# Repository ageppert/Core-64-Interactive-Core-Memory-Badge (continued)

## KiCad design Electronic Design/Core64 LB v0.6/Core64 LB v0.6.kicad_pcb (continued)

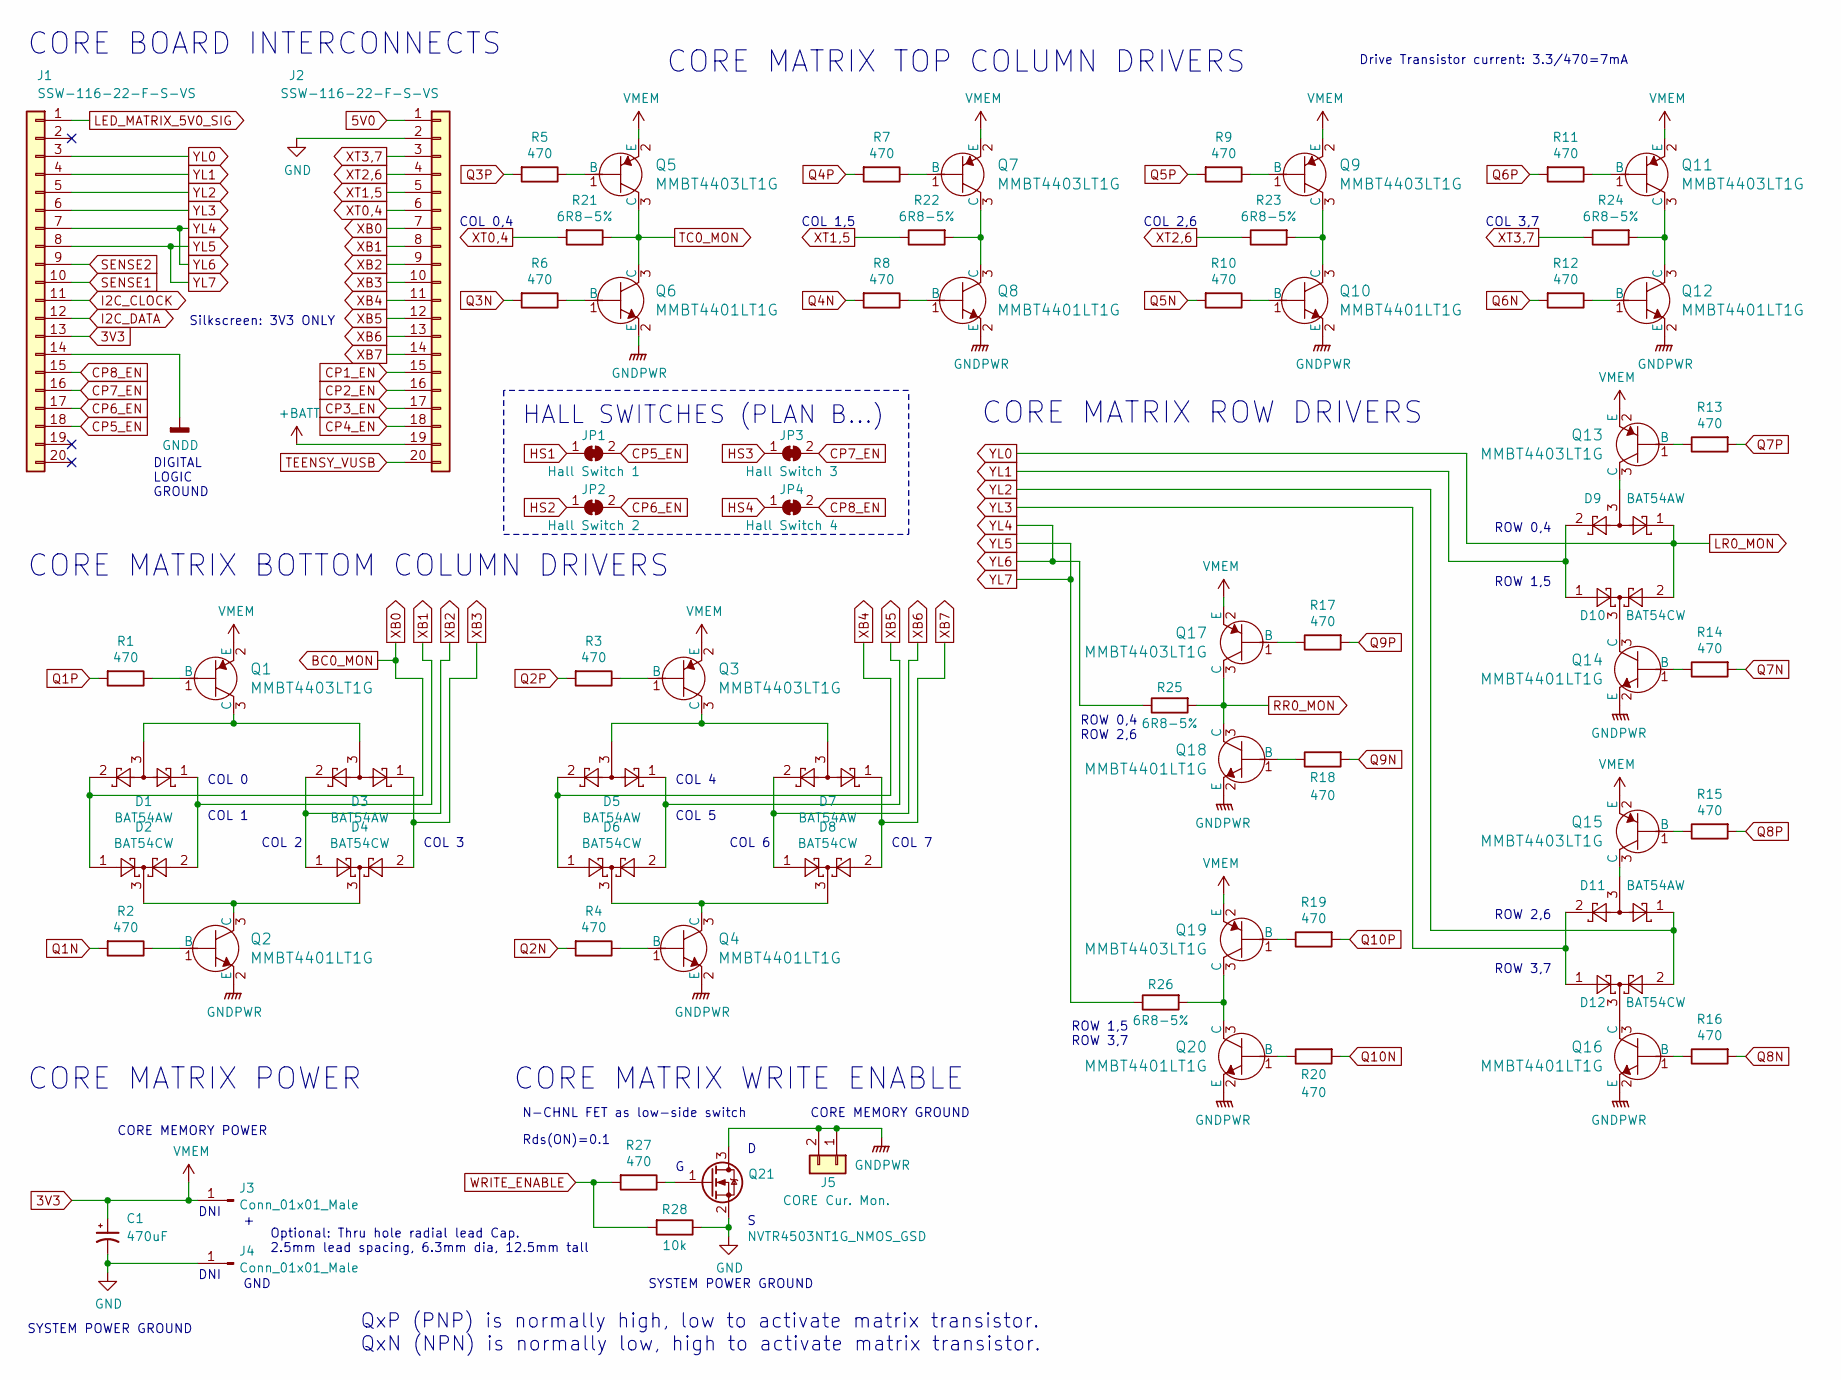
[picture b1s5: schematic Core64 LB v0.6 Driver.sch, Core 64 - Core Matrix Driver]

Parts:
C1: 470uF; CP_Elec_6.3x7.7; MPN(Secondary) 6.3SEV330M6.3X8; Digikey 565-EMHL100ARA471MHA0GCT-ND
D1, D3, D5, D7, D9, D11: BAT54AW; SOT-323_SC-70; MPN BAT54AW-7-F
D2, D4, D6, D8, D10, D12: BAT54CW; SOT-323_SC-70; MPN BAT54CW-7-F
J1, J2: SSW-116-22-F-S-VS‎; PinSocket_1x20_P2.54mm_Vertical
J3, J4: Conn_01x01_Male; PinHeader_1x01_P2.54mm_Vertical_No_Registration
J5: CORE Cur. Mon.; PinSocket_1x02_P2.54mm_Vertical
JP1: Hall Switch 1; SolderJumper-2_P1.3mm_Bridged_RoundedPad1.0x1.5mm
JP2: Hall Switch 2; SolderJumper-2_P1.3mm_Bridged_RoundedPad1.0x1.5mm
JP3: Hall Switch 3; SolderJumper-2_P1.3mm_Bridged_RoundedPad1.0x1.5mm
JP4: Hall Switch 4; SolderJumper-2_P1.3mm_Bridged_RoundedPad1.0x1.5mm
Q1, Q3, Q5, Q7, Q9, Q11, Q13, Q15, Q17, Q19: MMBT4403LT1G; SOT-23-3; MPN MMBT4403LT1G; Digi-Key_PN MMBT4403LT1GOSCT-ND
Q2, Q4, Q6, Q8, Q10, Q12, Q14, Q16, Q18, Q20: MMBT4401LT1G; SOT-23-3; MPN MMBT4401LT1G; Digi-Key_PN MMBT4401LT1GOSCT-ND
Q21: NVTR4503NT1G_NMOS_GSD; SOT-23-3; MPN NVTR4503NT1G
R1, R2, R3, R4, R5, R6, R7, R8, R9, R10, R11, R12, R13, R14, R15, R16, R17, R18, R19, R20, R27: 470; R_0805_2012Metric
R21, R22, R23, R24, R25, R26: 6R8-5%; R_0805_2012Metric
R28: 10k; R_0805_2012Metric

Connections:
3V3: C1.1, J1.13, J3.1, Q1.2 (E), Q3.2 (E), Q5.2 (E), Q7.2 (E), Q9.2 (E), Q11.2 (E), Q13.2 (E), Q15.2 (E), Q17.2 (E), Q19.2 (E); also elsewhere on the board
5V0: J2.1; also elsewhere on the board
+BATT: J2.19; also elsewhere on the board
BC0_MON: D1.2, D2.1, J2.7; also elsewhere on the board
CP1_EN: J2.15; also elsewhere on the board
CP2_EN: J2.16; also elsewhere on the board
CP3_EN: J2.17; also elsewhere on the board
CP4_EN: J2.18; also elsewhere on the board
GNDPWR: J5.1, J5.2, Q2.2 (E), Q4.2 (E), Q6.2 (E), Q8.2 (E), Q10.2 (E), Q12.2 (E), Q14.2 (E), Q16.2 (E), Q18.2 (E), Q20.2 (E), Q21.3 (D)
I2C_CLOCK: J1.11; also elsewhere on the board
I2C_DATA: J1.12; also elsewhere on the board
IR_OUT: R4.2; also elsewhere on the board
LED_MATRIX_5V0_SIG: J1.1; also elsewhere on the board
LR0_MON: D9.1, D10.2, J1.3; also elsewhere on the board
unnamed: D1.3, D3.3, Q1.3 (C)
unnamed: D2.3, D4.3, Q2.3 (C)
unnamed: D5.3, D7.3, Q3.3 (C)
unnamed: D6.3, D8.3, Q4.3 (C)
unnamed: D9.3, Q13.3 (C)
unnamed: D10.3, Q14.3 (C)
unnamed: D11.3, Q15.3 (C)
unnamed: D12.3, Q16.3 (C)
unnamed: Q1.1 (B), R1.1
unnamed: Q2.1 (B), R2.1
unnamed: Q3.1 (B), R3.1
unnamed: Q4.1 (B), R4.1
unnamed: Q5.1 (B), R5.1
unnamed: Q6.1 (B), R6.1
unnamed: Q7.1 (B), R7.1
unnamed: Q7.3 (C), Q8.3 (C), R22.2
unnamed: Q8.1 (B), R8.1
unnamed: Q9.1 (B), R9.1
unnamed: Q10.1 (B), R10.1
unnamed: Q9.3 (C), Q10.3 (C), R23.2
unnamed: Q11.1 (B), R11.1
unnamed: Q11.3 (C), Q12.3 (C), R24.2
unnamed: Q12.1 (B), R12.1
unnamed: Q13.1 (B), R13.1
unnamed: Q14.1 (B), R14.1
unnamed: Q15.1 (B), R15.1
unnamed: Q16.1 (B), R16.1
unnamed: Q17.1 (B), R17.1
unnamed: Q18.1 (B), R18.1
unnamed: Q19.1 (B), R19.1
unnamed: Q19.3 (C), Q20.3 (C), R26.2
unnamed: Q20.1 (B), R20.1
unnamed: Q21.1 (G), R27.1
OLED_SPI_CS: R1.2; also elsewhere on the board
OLED_SPI_DC: R27.2, R28.2; also elsewhere on the board
Q1N: R2.2; also elsewhere on the board
Q2P: R3.2; also elsewhere on the board
Q3N: R6.2; also elsewhere on the board
Q3P: R5.2; also elsewhere on the board
Q4N: R8.2; also elsewhere on the board
Q4P: R7.2; also elsewhere on the board
Q5N: R10.2; also elsewhere on the board
Q5P: R9.2; also elsewhere on the board
Q6N: R12.2; also elsewhere on the board
Q6P: R11.2; also elsewhere on the board
Q7N: R14.2; also elsewhere on the board
Q7P: R13.2; also elsewhere on the board
Q8N: R16.2; also elsewhere on the board
Q8P: R15.2; also elsewhere on the board
Q9N: R18.2; also elsewhere on the board
Q9P: R17.2; also elsewhere on the board
Q10N: R20.2; also elsewhere on the board
Q10P: R19.2; also elsewhere on the board
RR0_MON: Q17.3 (C), Q18.3 (C), R25.2; also elsewhere on the board
SENSE2: J1.9; also elsewhere on the board
TC0_MON: Q5.3 (C), Q6.3 (C), R21.1; also elsewhere on the board
TEENSY_VUSB: J2.20; also elsewhere on the board
XB1: D1.1, D2.2, J2.8
XB2: D3.2, D4.1, J2.9
XB3: D3.1, D4.2, J2.10
XB4: D5.2, D6.1, J2.11
XB5: D5.1, D6.2, J2.12
XB6: D7.2, D8.1, J2.13
XB7: D7.1, D8.2, J2.14
XT0,4: J2.6, R21.2
XT1,5: J2.5, R22.1
XT2,6: J2.4, R23.1
XT3,7: J2.3, R24.1
YL1: D9.2, D10.1, J1.4
YL2: D11.1, D12.2, J1.5
YL3: D11.2, D12.1, J1.6
YL4: J1.7, R25.1
YL5: J1.8, R26.1

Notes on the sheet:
COL 0,4
COL 1,5
COL 2,6
COL 3,7
COL 0
COL 1
COL 2
COL 3
COL 4
COL 5
COL 6
COL 7
ROW 0,4 ROW 2,6
ROW 1,5 ROW 3,7
ROW 0,4
ROW 3,7
ROW 1,5
ROW 2,6
CORE MEMORY GROUND
CORE MEMORY POWER
CORE MATRIX POWER
CORE MATRIX BOTTOM COLUMN DRIVERS
CORE MATRIX TOP COLUMN DRIVERS
CORE MATRIX ROW DRIVERS
CORE MATRIX WRITE ENABLE
DIGITAL LOGIC GROUND
SYSTEM POWER GROUND
CORE BOARD INTERCONNECTS
Silkscreen: 3V3 ONLY
QxP (PNP) is normally high, low to activate matrix transistor. QxN (NPN) is normally low, high to activate matrix transistor.
N-CHNL FET as low-side switch
Rds(ON)=0.1
Drive Transistor current: 3.3/470=7mA
HALL SWITCHES (PLAN B…)
GND
DNI
Optional: Thru hole radial lead Cap. 2.5mm lead spacing, 6.3mm dia, 12.5mm tall

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
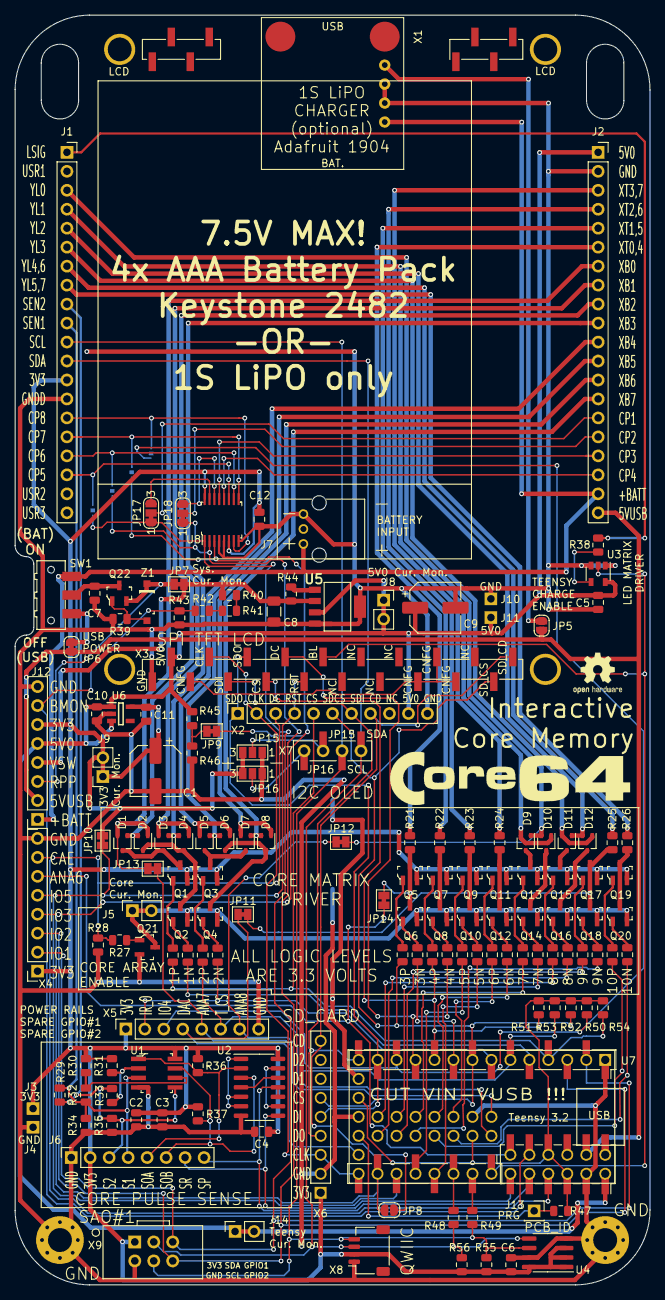
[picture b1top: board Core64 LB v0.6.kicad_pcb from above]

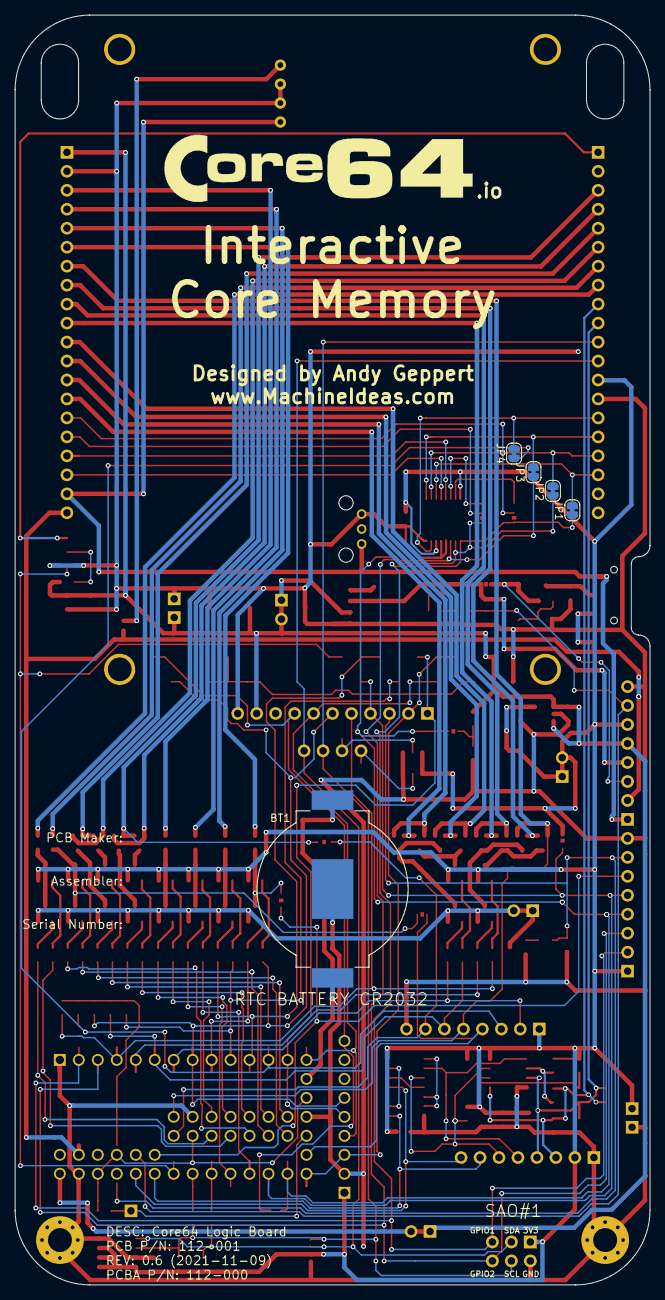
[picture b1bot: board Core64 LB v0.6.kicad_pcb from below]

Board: 2 copper layers, 85.0 x 170.0 mm, 159 parts (6 on the bottom side), 138 nets.

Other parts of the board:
JP15, JP16: SolderJumper_3_Open; SolderJumper-3_P1.3mm_Open_Pad1.0x1.5mm_NumberLabels
JP17, JP18: SolderJumper_3_Open; SolderJumper-3_P1.3mm_Bridged12_RoundedPad1.0x1.5mm_NumberL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
U8: 74HC238; TSSOP-16-W4.40mm

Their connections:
3V3: JP15.3, JP16.3, U8.6, U8.16; also elsewhere on the board
CP1_EN: JP17.2; also elsewhere on the board
CP2_EN: JP18.2; also elsewhere on the board
CP3_EN: U8.13; also elsewhere on the board
CP4_EN: U8.12; also elsewhere on the board
unnamed: JP17.3, U8.15
unnamed: JP18.3, U8.14

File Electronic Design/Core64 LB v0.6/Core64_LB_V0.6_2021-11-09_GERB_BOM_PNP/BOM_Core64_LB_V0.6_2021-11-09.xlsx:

Reference | Quantity | Value | Value_Modifier | Footprint | Description | Manufacturer (Primary) | Manuf. P/N (Primary) | Manufacturer (Secondary) | Manuf. P/N (Secondary)
C1, C9 | 2 | 470uF | 330UF 20% 6.3V | Capacitor_SMD:CP_Elec_6.3x7.7 | CAP ALUM 470UF 20% 10V SMD. (or 330UF 20% 6.3V) | Panasonic | EEE-FTA471XAL | Rubycon | 6.3SEV330M6.3X8
C2, C4-C6 | 4 | 0.1uF | X7R or X5R ceramic | Capacitor_SMD:C_0805_2012Metric | CAP | Any
C3 | 1 | 10uF | X7R or X5R ceramic | Capacitor_SMD:C_0805_2012Metric | CAP | Any
C8 | 1 | 68uF | X7R or X5R ceramic | Capacitor_SMD:C_1206_3216Metric | CAP | TDK | C3216X5R1A686M160AC
C10, C11 | 2 | 1uF | X7R or X5R ceramic | Capacitor_SMD:C_0805_2012Metric | CAP | Any
D1, D3, D5, D7, D9, D11 | 6 | BAT54AW |  | Package_TO_SOT_SMD:SOT-323_SC-70 | DIODE ARRAY SCHOTTKY 30V | Diodes Inc. | BAT54AW-7-F
D2, D4, D6, D8, D10, D12 | 6 | BAT54CW |  | Package_TO_SOT_SMD:SOT-323_SC-70 | DIODE ARRAY SCHOTTKY 30V | Diodes Inc. | BAT54CW-7-F
Q1, Q3, Q5, Q7, Q9, Q11, Q13, Q15, Q17, Q19 | 10 | MMBT4403LT1G |  | Digikey:SOT-23-3 | TRANS PNP 40V 0.6A SOT23 | Onsemi | MMBT4403LT1G | Diodes Inc. | MMBT4403-7-F
Q2, Q4, Q6, Q8, Q10, Q12, Q14, Q16, Q18, Q20 | 10 | MMBT4401LT1G |  | Digikey:SOT-23-3 | TRANS NPN 40V 0.6A SOT23 | Onsemi | MMBT4401LT1G | Diodes Inc. | MMBT4401-7-F
Q21 | 1 | NVTR4503NT1G_NMOS_GSD |  | Digikey:SOT-23-3 | MOSFET N-CHNL GSD LOW RDS(ON) | Onsemi | NVTR4503NT1G | Infineon Technologies | IRLML2030TRPBF
Q22 | 1 | MCC_SL3401A_PMOS_GSD |  | Digikey:SOT-23-3 | MOSFET P-CHNL GSD LOW RDS(ON) | Micro Commercial Co | SL3401A-TP | Diodes Inc. | DMP3125L-7
R1-R20, R27, R38 | 22 | 470 | 0.1 | Resistor_SMD:R_0805_2012Metric | RES 470 OHM | Any
R21-R26 | 6 | 6R8-5% | 0.05 | Resistor_SMD:R_0805_2012Metric | RES 6.8 OHM 1/8W 0805 | Any
R28, R39, R44, R47, R40-R43, R45, R46 | 10 | 10k | 0.2 | Resistor_SMD:R_0805_2012Metric | RES 10K OHM | Any
R30, R31 | 2 | 1K8-1% | 0.01 | Resistor_SMD:R_0805_2012Metric | RES 1.8K OHM | Any
R32, R33 | 2 | 11-1% | 0.01 | Resistor_SMD:R_0805_2012Metric | RES 1 OHM | Any
R34, R35 | 2 | 1K5-1% | 0.01 | Resistor_SMD:R_0805_2012Metric | RES 1.5K OHM | Any
R36, R37, R55, R56 | 4 | 1K2 | 0.1 | Resistor_SMD:R_0805_2012Metric | RES 1.2K OHM | Any
R48, R49 | 2 | 68 | 0.1 | Resistor_SMD:R_0805_2012Metric | RES 68 OHM | Any
SW1 | 1 | JS102011SAQN |  | Button_Switch_SMD:SW_SPDT_CK-JS102011SAQN_Core64_Recessed | SWITCH SLIDE SPDT 300MA 6V | C&K | JS102011SAQN
U1 | 1 | LM393 |  | Digikey:SOIC-8_W3.9mm | IC COMPARATOR LP DUAL 8-SOIC | STMicroelectronics | LM393DT | Rohm | LM393DR
U2 | 1 | SN74HC02DR |  | Package_SO:SOIC-14_3.9x8.7mm_P1.27mm | IC GATE NOR 4CH 2-INP 14SOIC | Texas Instruments | SN74HC02DR
U3 | 1 | SN74LV1T125DBVR |  | Package_TO_SOT_SMD:SOT-23-5 | IC BUF NON-INVERT 5.5V SOT23-5 | Texas Instruments | SN74LV1T125DBVR | OnSemi | M74VHC1GT125DT1G
U4 | 1 | M24C02-RMN |  | Package_SO:SOIC-8_3.9x4.9mm_P1.27mm | IC EEPROM 2KBIT I2C 400KHZ 8SO | STMicroelectronics | M24C02-WMN6TP
U5 | 1 | LP3961EMP-5.0 |  | LP3961EMP-5.0:SOT150P696X180-5N | Fast Ultra Low Dropout Linear Regulators | Texas Instruments | LP3961EMP-5.0 |  | 926-LP3961EMP-50
U6 | 1 | TPS7A0533PDBVR |  | TPS7A0533PDBVR:SOT95P280X145-5N | Linear Voltage Regulator IC Positive Fixed 1 Output 200mA SOT-23-5 | Texas Instruments | TPS7A0533PDBVR | Texas Instruments | TPS7A0533PDBVT |  |  |  |  |  |  |  |  |  |  |  |  |  |  |  |  | TPS7A0533PDBVR
X8 | 1 | QWIIC |  | Connector_JST:JST_SH_SM04B-SRSS-TB_1x04-1MP_P1.00mm_Horizontal | CONN HEADER SMD R/A 4POS 1MM | JST | SM04B-SRSS-TB(LF)(SN)

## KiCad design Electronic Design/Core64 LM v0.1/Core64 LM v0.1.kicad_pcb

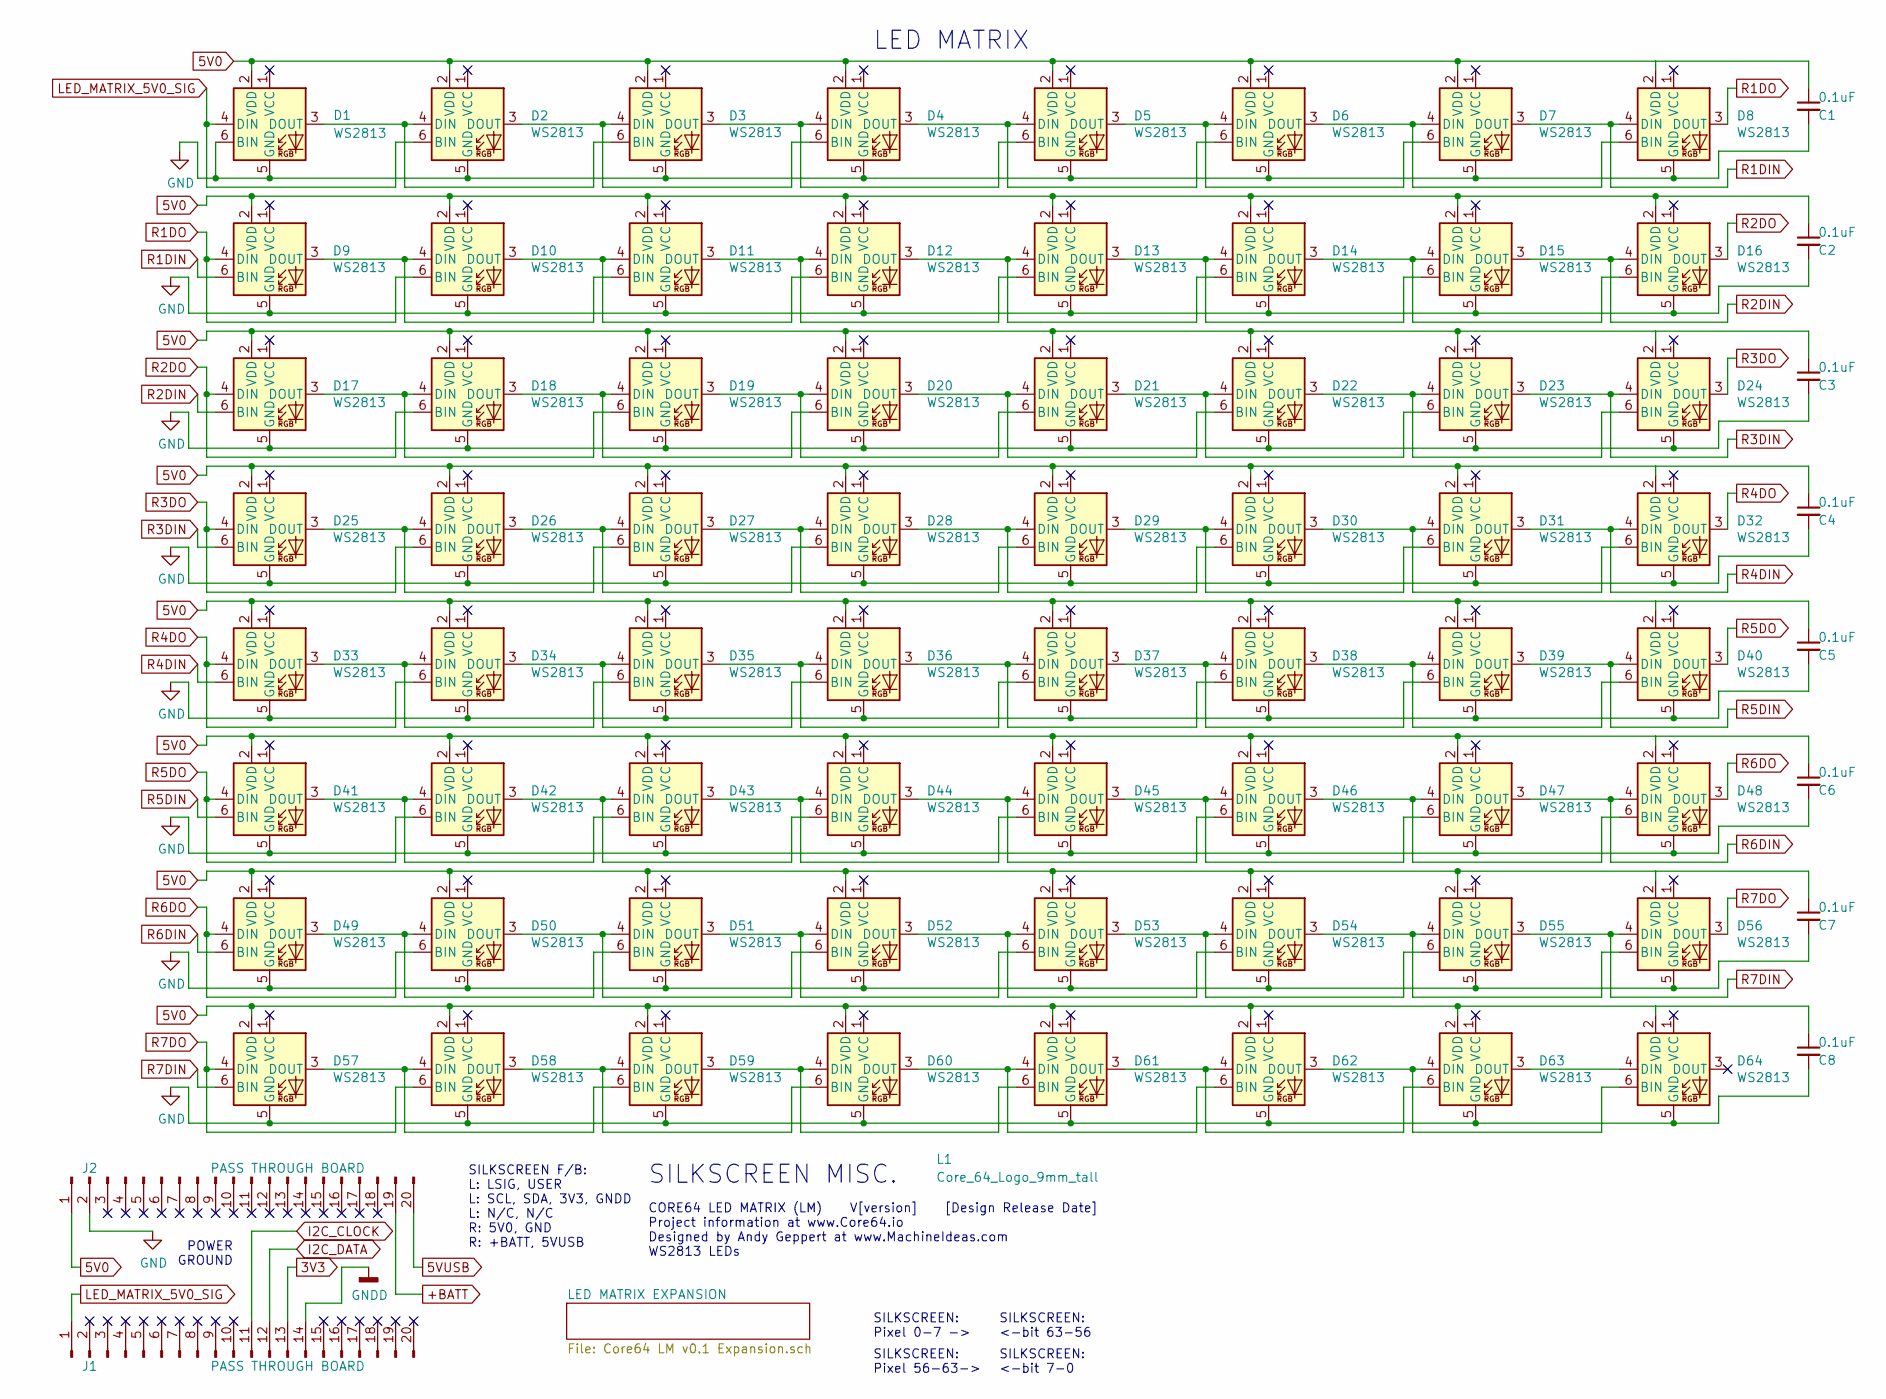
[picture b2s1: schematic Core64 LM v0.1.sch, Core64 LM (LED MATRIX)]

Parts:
C1, C2, C3, C4, C5, C6, C7, C8: 0.1uF; C_0603_1608Metric
D1, D2, D3, D4, D5, D6, D7, D8, D9, D10, D11, D12, D13, D14, D15, D16, D17, D18, D19, D20, D21, D22, D23, D24, D25, D26, D27, D28, D29, D30, D31, D32, D33, D34, D35, D36, D37, D38, D39, D40, D41, D42, D43, D44, D45, D46, D47, D48, D49, D50, D51, D52, D53, D54, D55, D56, D57, D58, D59, D60, D61, D62, D63, D64: WS2813; LED_WS2813_PLCC6_5.0x5.0mm_P1.6mm_Core64_Abg_Mod
J1, J2: PASS THROUGH BOARD; PinHeader_1x20_P2.54mm_Vertical_SMD_and_TH_Pin1Right
L1: Core_64_Logo_9mm_tall; Core64_Logo_9mm_tall

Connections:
3V3: J1.13; also elsewhere on the board
5V0: C1.1, C2.1, C3.1, C4.1, C5.1, C6.1, C7.1, C8.1, D1.2 (VDD), D2.2 (VDD), D3.2 (VDD), D4.2 (VDD), D5.2 (VDD), D6.2 (VDD), D7.2 (VDD), D8.2 (VDD), D9.2 (VDD), D10.2 (VDD), D11.2 (VDD), D12.2 (VDD), D13.2 (VDD), D14.2 (VDD), D15.2 (VDD), D16.2 (VDD), D17.2 (VDD), D18.2 (VDD), D19.2 (VDD), D20.2 (VDD), D21.2 (VDD), D22.2 (VDD), D23.2 (VDD), D24.2 (VDD), D25.2 (VDD), D26.2 (VDD), D27.2 (VDD), D28.2 (VDD), D29.2 (VDD), D30.2 (VDD), D31.2 (VDD), D32.2 (VDD), D33.2 (VDD), D34.2 (VDD), D35.2 (VDD), D36.2 (VDD), D37.2 (VDD), D38.2 (VDD), D39.2 (VDD), D40.2 (VDD), D41.2 (VDD), D42.2 (VDD), D43.2 (VDD), D44.2 (VDD), D45.2 (VDD), D46.2 (VDD), D47.2 (VDD), D48.2 (VDD), D49.2 (VDD), D50.2 (VDD), D51.2 (VDD), D52.2 (VDD), D53.2 (VDD), D54.2 (VDD), D55.2 (VDD), D56.2 (VDD), D57.2 (VDD), D58.2 (VDD), D59.2 (VDD), D60.2 (VDD), D61.2 (VDD), D62.2 (VDD), D63.2 (VDD), D64.2 (VDD), J2.1; also elsewhere on the board
5VUSB: J2.20; also elsewhere on the board
+BATT: J2.19; also elsewhere on the board
GND: C1.2, C2.2, C3.2, C4.2, C5.2, C6.2, C7.2, C8.2, D1.5 (GND), D1.6 (BIN), D2.5 (GND), D3.5 (GND), D4.5 (GND), D5.5 (GND), D6.5 (GND), D7.5 (GND), D8.5 (GND), D9.5 (GND), D10.5 (GND), D11.5 (GND), D12.5 (GND), D13.5 (GND), D14.5 (GND), D15.5 (GND), D16.5 (GND), D17.5 (GND), D18.5 (GND), D19.5 (GND), D20.5 (GND), D21.5 (GND), D22.5 (GND), D23.5 (GND), D24.5 (GND), D25.5 (GND), D26.5 (GND), D27.5 (GND), D28.5 (GND), D29.5 (GND), D30.5 (GND), D31.5 (GND), D32.5 (GND), D33.5 (GND), D34.5 (GND), D35.5 (GND), D36.5 (GND), D37.5 (GND), D38.5 (GND), D39.5 (GND), D40.5 (GND), D41.5 (GND), D42.5 (GND), D43.5 (GND), D44.5 (GND), D45.5 (GND), D46.5 (GND), D47.5 (GND), D48.5 (GND), D49.5 (GND), D50.5 (GND), D51.5 (GND), D52.5 (GND), D53.5 (GND), D54.5 (GND), D55.5 (GND), D56.5 (GND), D57.5 (GND), D58.5 (GND), D59.5 (GND), D60.5 (GND), D61.5 (GND), D62.5 (GND), D63.5 (GND), D64.5 (GND), J2.2; also elsewhere on the board
GNDD: J1.14; also elsewhere on the board
I2C_CLOCK: J1.11; also elsewhere on the board
I2C_DATA: J1.12; also elsewhere on the board
LED_MATRIX_5V0_SIG: D1.4 (DIN), D2.6 (BIN), J1.1; also elsewhere on the board
unnamed: D1.3 (DOUT), D2.4 (DIN), D3.6 (BIN)
unnamed: D2.3 (DOUT), D3.4 (DIN), D4.6 (BIN)
unnamed: D3.3 (DOUT), D4.4 (DIN), D5.6 (BIN)
unnamed: D4.3 (DOUT), D5.4 (DIN), D6.6 (BIN)
unnamed: D5.3 (DOUT), D6.4 (DIN), D7.6 (BIN)
unnamed: D6.3 (DOUT), D7.4 (DIN), D8.6 (BIN)
unnamed: D10.3 (DOUT), D11.4 (DIN), D12.6 (BIN)
unnamed: D9.3 (DOUT), D10.4 (DIN), D11.6 (BIN)
unnamed: D11.3 (DOUT), D12.4 (DIN), D13.6 (BIN)
unnamed: D12.3 (DOUT), D13.4 (DIN), D14.6 (BIN)
unnamed: D13.3 (DOUT), D14.4 (DIN), D15.6 (BIN)
unnamed: D14.3 (DOUT), D15.4 (DIN), D16.6 (BIN)
unnamed: D17.3 (DOUT), D18.4 (DIN), D19.6 (BIN)
unnamed: D18.3 (DOUT), D19.4 (DIN), D20.6 (BIN)
unnamed: D19.3 (DOUT), D20.4 (DIN), D21.6 (BIN)
unnamed: D20.3 (DOUT), D21.4 (DIN), D22.6 (BIN)
unnamed: D21.3 (DOUT), D22.4 (DIN), D23.6 (BIN)
unnamed: D22.3 (DOUT), D23.4 (DIN), D24.6 (BIN)
unnamed: D25.3 (DOUT), D26.4 (DIN), D27.6 (BIN)
unnamed: D26.3 (DOUT), D27.4 (DIN), D28.6 (BIN)
unnamed: D27.3 (DOUT), D28.4 (DIN), D29.6 (BIN)
unnamed: D28.3 (DOUT), D29.4 (DIN), D30.6 (BIN)
unnamed: D29.3 (DOUT), D30.4 (DIN), D31.6 (BIN)
unnamed: D30.3 (DOUT), D31.4 (DIN), D32.6 (BIN)
unnamed: D33.3 (DOUT), D34.4 (DIN), D35.6 (BIN)
unnamed: D34.3 (DOUT), D35.4 (DIN), D36.6 (BIN)
unnamed: D35.3 (DOUT), D36.4 (DIN), D37.6 (BIN)
unnamed: D36.3 (DOUT), D37.4 (DIN), D38.6 (BIN)
unnamed: D37.3 (DOUT), D38.4 (DIN), D39.6 (BIN)
unnamed: D38.3 (DOUT), D39.4 (DIN), D40.6 (BIN)
unnamed: D41.3 (DOUT), D42.4 (DIN), D43.6 (BIN)
unnamed: D42.3 (DOUT), D43.4 (DIN), D44.6 (BIN)
unnamed: D43.3 (DOUT), D44.4 (DIN), D45.6 (BIN)
unnamed: D44.3 (DOUT), D45.4 (DIN), D46.6 (BIN)
unnamed: D45.3 (DOUT), D46.4 (DIN), D47.6 (BIN)
unnamed: D46.3 (DOUT), D47.4 (DIN), D48.6 (BIN)
unnamed: D49.3 (DOUT), D50.4 (DIN), D51.6 (BIN)
unnamed: D50.3 (DOUT), D51.4 (DIN), D52.6 (BIN)
unnamed: D51.3 (DOUT), D52.4 (DIN), D53.6 (BIN)
unnamed: D52.3 (DOUT), D53.4 (DIN), D54.6 (BIN)
unnamed: D53.3 (DOUT), D54.4 (DIN), D55.6 (BIN)
unnamed: D54.3 (DOUT), D55.4 (DIN), D56.6 (BIN)
unnamed: D57.3 (DOUT), D58.4 (DIN), D59.6 (BIN)
unnamed: D58.3 (DOUT), D59.4 (DIN), D60.6 (BIN)
unnamed: D59.3 (DOUT), D60.4 (DIN), D61.6 (BIN)
unnamed: D60.3 (DOUT), D61.4 (DIN), D62.6 (BIN)
unnamed: D61.3 (DOUT), D62.4 (DIN), D63.6 (BIN)
unnamed: D62.3 (DOUT), D63.4 (DIN), D64.6 (BIN)
unnamed: D63.3 (DOUT), D64.4 (DIN)
R1DIN: D7.3 (DOUT), D8.4 (DIN), D9.6 (BIN)
R1DO: D8.3 (DOUT), D9.4 (DIN), D10.6 (BIN)
R2DIN: D15.3 (DOUT), D16.4 (DIN), D17.6 (BIN)
R2DO: D16.3 (DOUT), D17.4 (DIN), D18.6 (BIN)
R3DIN: D23.3 (DOUT), D24.4 (DIN), D25.6 (BIN)
R3DO: D24.3 (DOUT), D25.4 (DIN), D26.6 (BIN)
R4DIN: D31.3 (DOUT), D32.4 (DIN), D33.6 (BIN)
R4DO: D32.3 (DOUT), D33.4 (DIN), D34.6 (BIN)
R5DIN: D39.3 (DOUT), D40.4 (DIN), D41.6 (BIN)
R5DO: D40.3 (DOUT), D41.4 (DIN), D42.6 (BIN)
R6DIN: D47.3 (DOUT), D48.4 (DIN), D49.6 (BIN)
R6DO: D48.3 (DOUT), D49.4 (DIN), D50.6 (BIN)
R7DIN: D55.3 (DOUT), D56.4 (DIN), D57.6 (BIN)
R7DO: D56.3 (DOUT), D57.4 (DIN), D58.6 (BIN)

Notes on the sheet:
SILKSCREEN F/B: L: LSIG, USER L: SCL, SDA, 3V3, GNDD L: N/C, N/C R: 5V0, GND R: +BATT, 5VUSB
POWER GROUND
LED MATRIX
SILKSCREEN: Pixel 0-7 ->
SILKSCREEN: <-bit 63-56
SILKSCREEN: <-bit 7-0
SILKSCREEN: Pixel 56-63->
CORE64 LED MATRIX (LM) V[version] [Design Release Date] Project information at www.Core64.io Designed by Andy Geppert at www.MachineIdeas.com WS2813 LEDs
SILKSCREEN MISC.

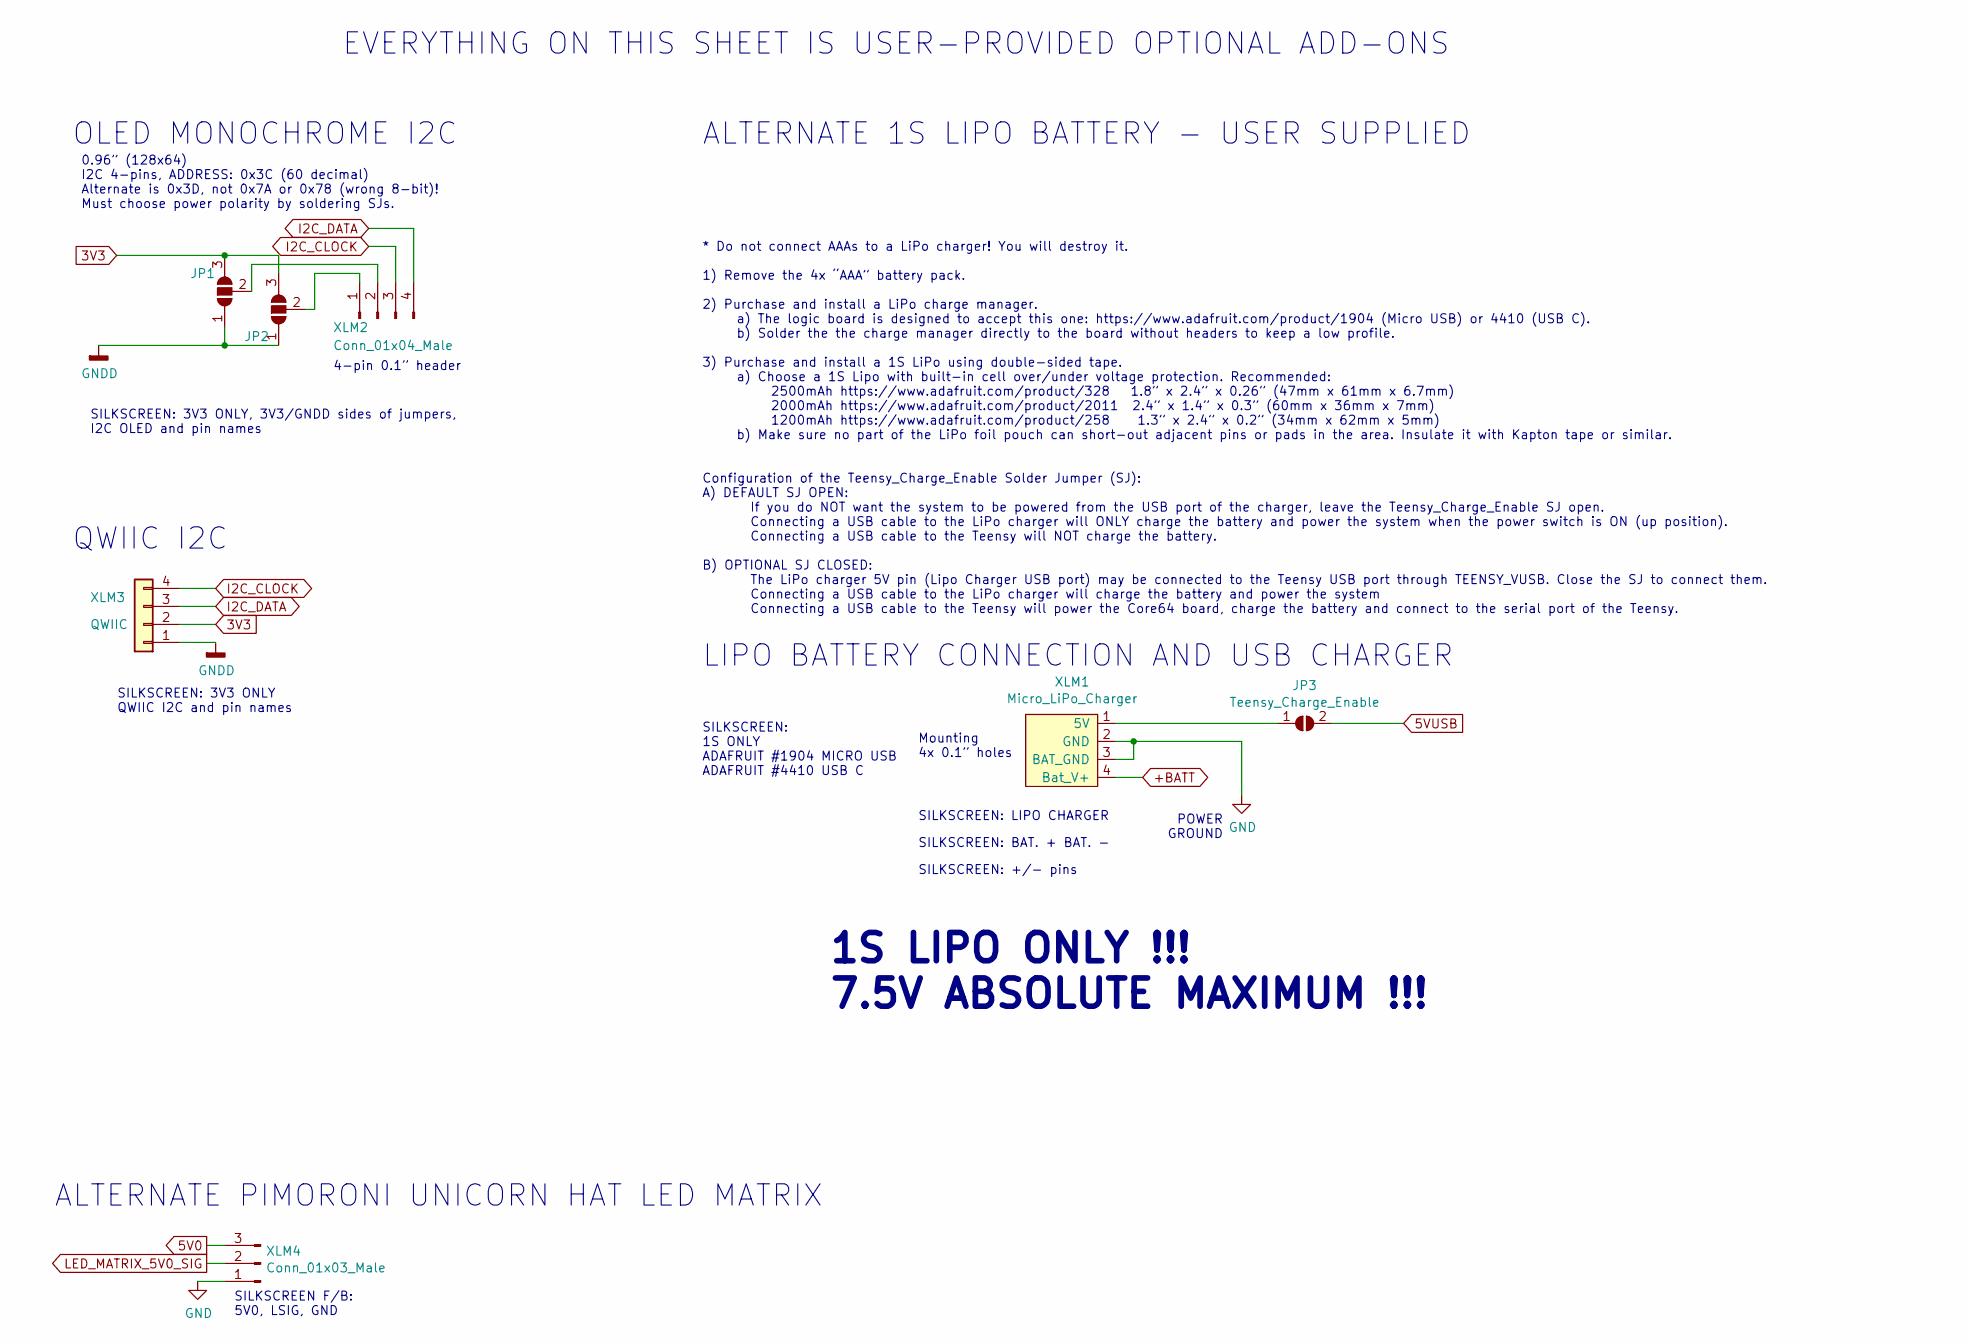
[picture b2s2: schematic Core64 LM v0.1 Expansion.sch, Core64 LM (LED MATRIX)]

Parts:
JP1, JP2: SolderJumper_3_Open; SolderJumper-3_P1.3mm_Open_Pad1.0x1.5mm_NumberLabels
JP3: Teensy_Charge_Enable; SolderJumper-2_P1.3mm_Open_Pad1.0x1.5mm
XLM1: Micro_LiPo_Charger; Micro_LiPo_Charger_CornerSMD
XLM2: Conn_01x04_Male; PinHeader_1x04_P2.54mm_Vertical
XLM3: QWIIC; JST_SH_SM04B-SRSS-TB_1x04-1MP_P1.00mm_Horizontal
XLM4: Conn_01x03_Male; PinHeader_1x03_P2.54mm_Vertical

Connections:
3V3: JP1.3 (B), JP2.3 (B), XLM3.2; also elsewhere on the board
5V0: XLM4.3; also elsewhere on the board
5VUSB: JP3.2 (B); also elsewhere on the board
+BATT: XLM1.4 (Bat_V+); also elsewhere on the board
GND: XLM1.2 (GND), XLM1.3 (BAT_GND), XLM4.1; also elsewhere on the board
GNDD: JP1.1 (A), JP2.1 (A), XLM3.1; also elsewhere on the board
I2C_CLOCK: XLM2.3, XLM3.4; also elsewhere on the board
I2C_DATA: XLM2.4, XLM3.3; also elsewhere on the board
LED_MATRIX_5V0_SIG: XLM4.2; also elsewhere on the board
unnamed: JP1.2 (C), XLM2.2
unnamed: JP2.2 (C), XLM2.1
unnamed: JP3.1 (A), XLM1.1 (5V)

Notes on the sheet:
OLED MONOCHROME I2C
0.96” (128x64) I2C 4-pins, ADDRESS: 0x3C (60 decimal) Alternate is 0x3D, not 0x7A or 0x78 (wrong 8-bit)! Must choose power polarity by soldering SJs.
QWIIC I2C
SILKSCREEN: 3V3 ONLY, 3V3/GNDD sides of jumpers, I2C OLED and pin names
4-pin 0.1” header
SILKSCREEN: 3V3 ONLY QWIIC I2C and pin names
SILKSCREEN F/B: 5V0, LSIG, GND
POWER GROUND
ALTERNATE PIMORONI UNICORN HAT LED MATRIX
LIPO BATTERY CONNECTION AND USB CHARGER
EVERYTHING ON THIS SHEET IS USER-PROVIDED OPTIONAL ADD-ONS
SILKSCREEN: 1S ONLY ADAFRUIT #1904 MICRO USB ADAFRUIT #4410 USB C
ALTERNATE 1S LIPO BATTERY - USER SUPPLIED
1S LIPO ONLY !!! 7.5V ABSOLUTE MAXIMUM !!!
SILKSCREEN: +/- pins
SILKSCREEN: LIPO CHARGER
SILKSCREEN: BAT. + BAT. -
Mounting 4x 0.1” holes
* Do not connect AAAs to a LiPo charger! You will destroy it. 1) Remove the 4x “AAA” battery pack. 2) Purchase and install a LiPo charge manager. a) The logic board is designed to accept this one: https://www.adafruit.com/product/1904 (Micro USB) or 4410 (USB C). b) Solder the the charge manager di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

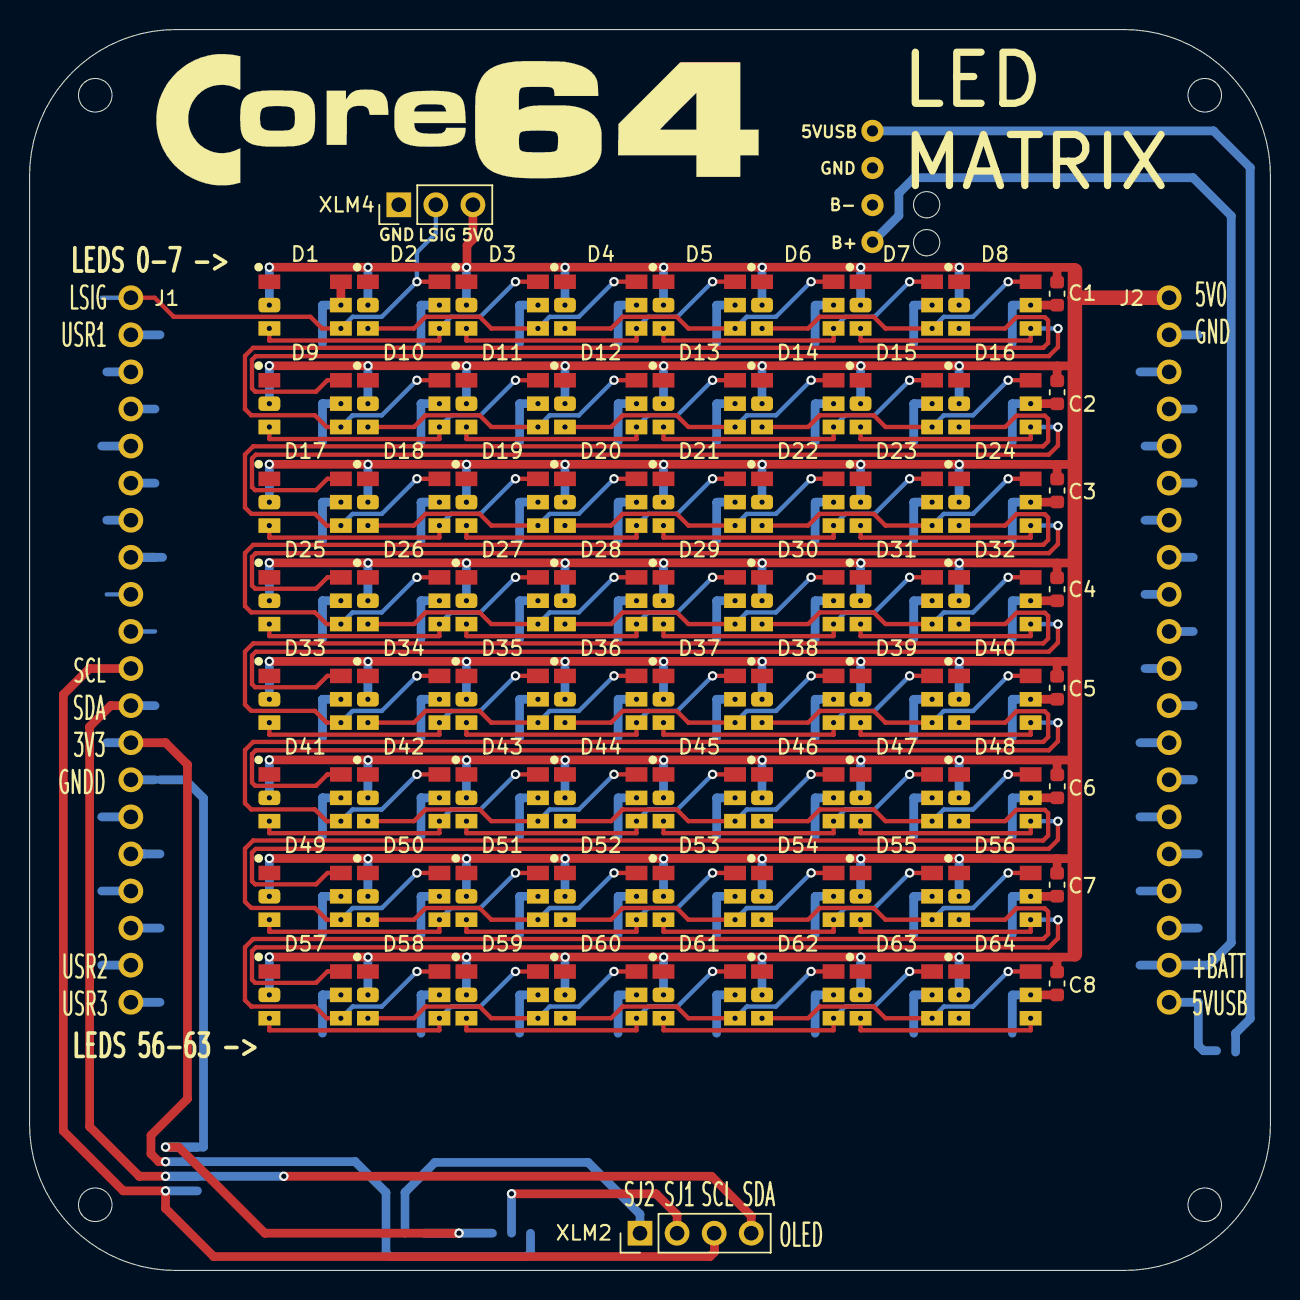
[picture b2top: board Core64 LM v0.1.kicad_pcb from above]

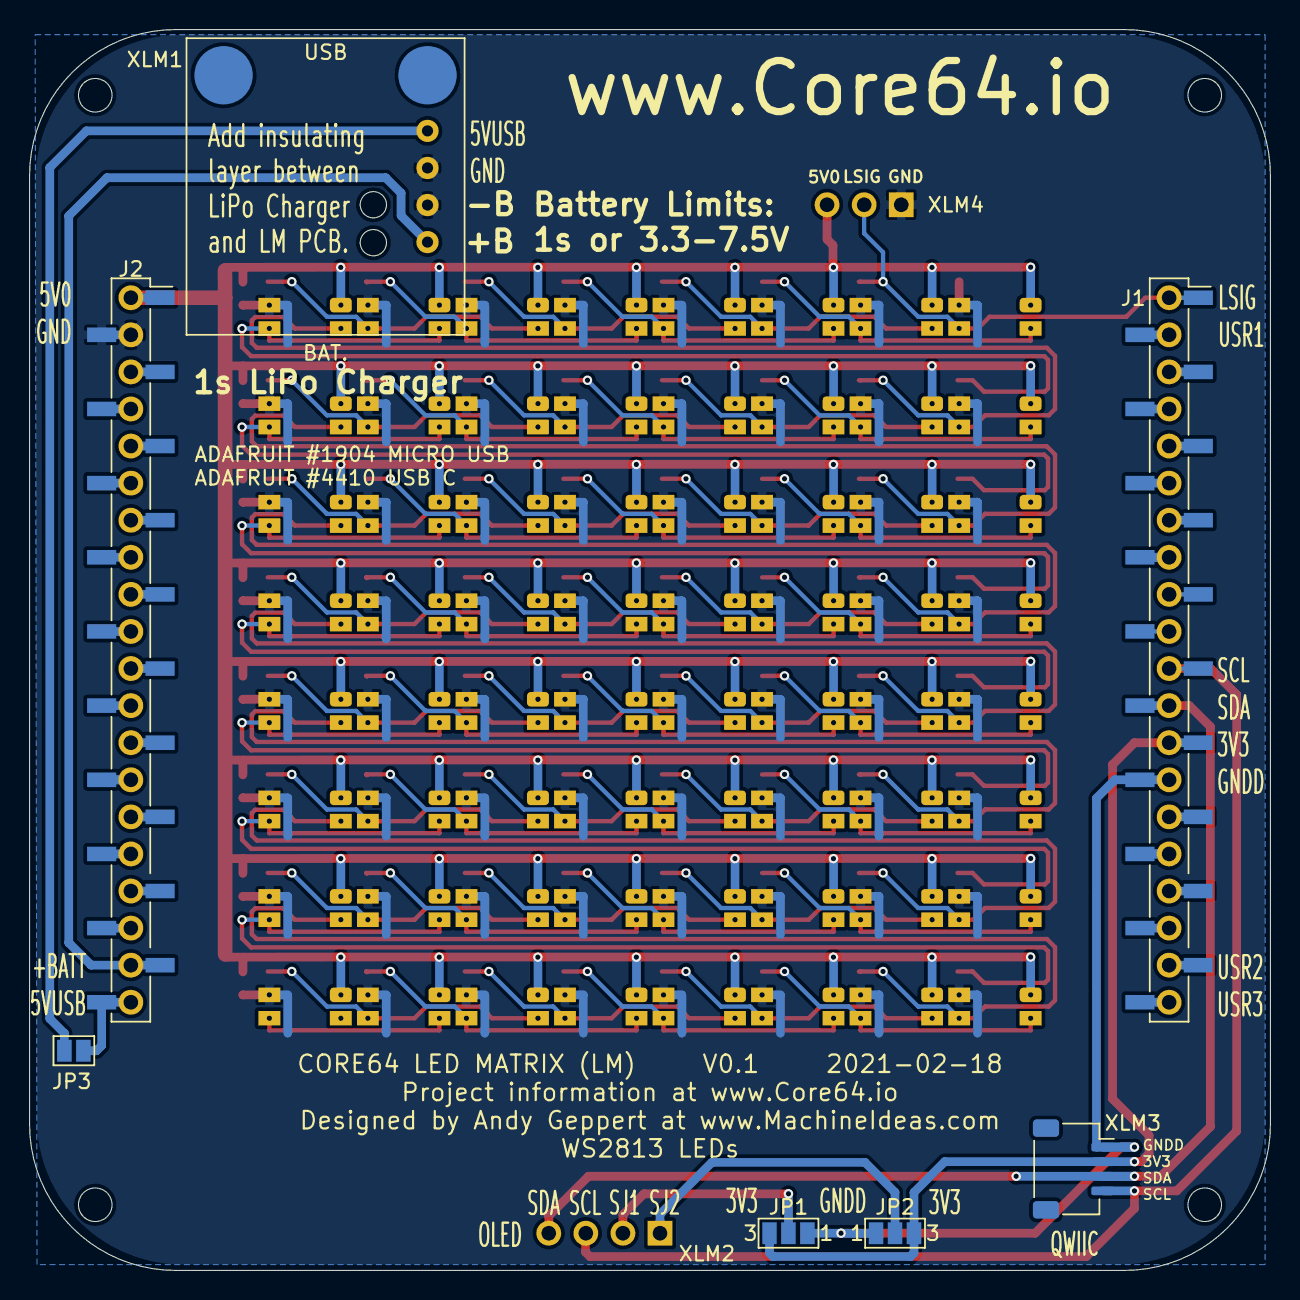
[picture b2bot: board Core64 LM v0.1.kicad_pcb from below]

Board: 2 copper layers, 85.0 x 85.0 mm, 82 parts (7 on the bottom side), 75 nets.
